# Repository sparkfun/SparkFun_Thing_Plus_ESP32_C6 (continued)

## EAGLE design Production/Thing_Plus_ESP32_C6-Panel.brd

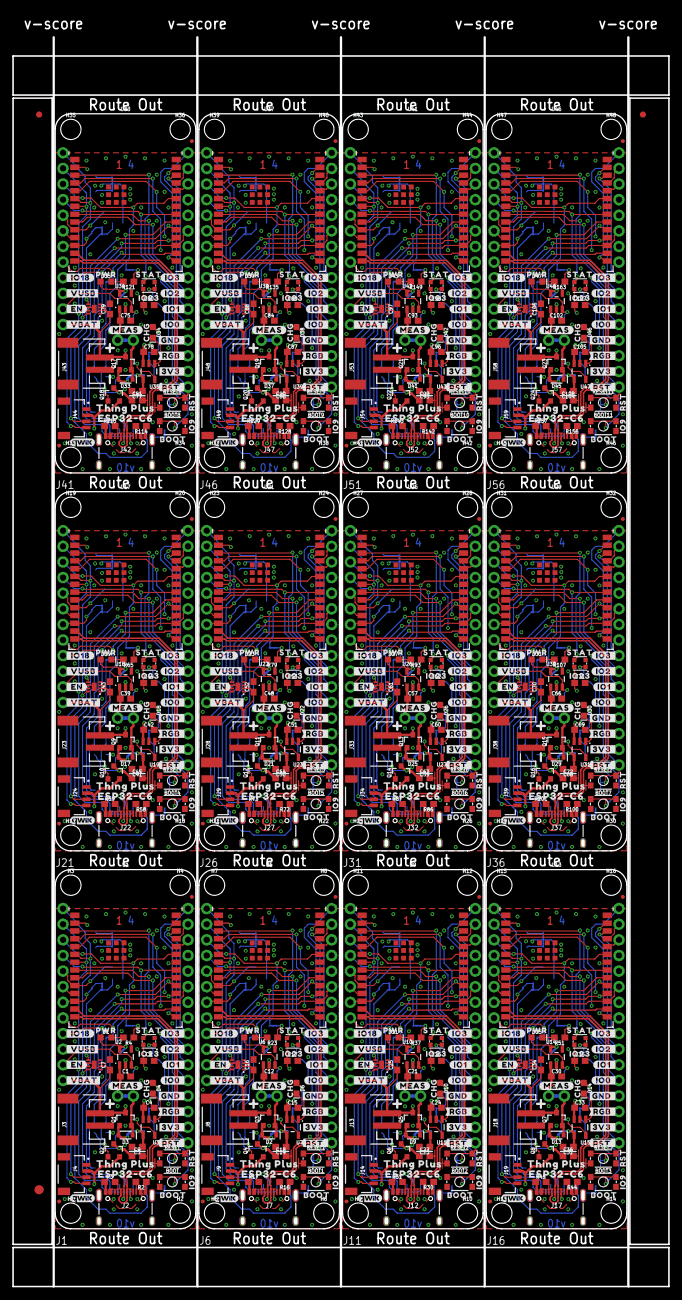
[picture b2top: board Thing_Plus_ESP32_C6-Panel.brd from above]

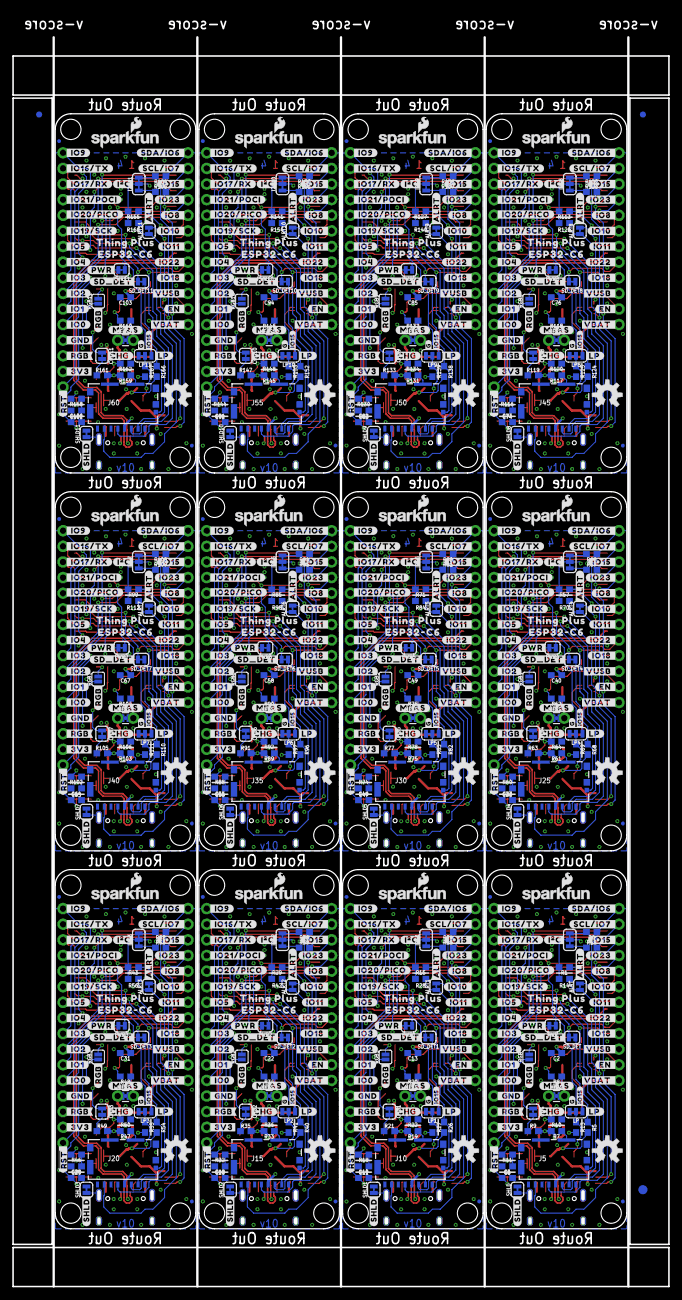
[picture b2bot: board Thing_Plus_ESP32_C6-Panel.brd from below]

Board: 4 copper layers, 106.7 x 203.2 mm, 1482 parts (831 on the bottom side), 576 nets.

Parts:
ALRT, ALRT1, ALRT2, ALRT3, ALRT4, ALRT5, ALRT6, ALRT7, ALRT8, ALRT9, ALRT10, ALRT11: JUMPER-SMT_2_NC_TRACE_SILK; SMT-JUMPER_2_NC_TRACE_SILK
BOOT, BOOT1, BOOT2, BOOT3, BOOT4, BOOT5, BOOT6, BOOT7, BOOT8, BOOT9, BOOT10, BOOT11: MOMENTARY-SWITCH-SPST-SMD-4.6X2.8MM; TACTILE_SWITCH_SMD_4.6X2.8MM
C1, C2, C3, C4, C12, C13, C14, C15, C21, C22, C23, C24, C30, C31, C32, C33, C39, C40, C41, C42, C48, C49, C50, C51, C57, C58, C59, C60, C66, C67, C68, C69, C75, C76, C77, C78, C84, C85, C86, C87, C93, C94, C95, C96, C102, C103, C104, C105: 2.2uF; 0603
C5, C7, C8, C10, C16, C17, C19, C25, C26, C28, C34, C35, C37, C43, C44, C46, C52, C53, C55, C61, C62, C64, C70, C71, C73, C79, C80, C82, C88, C89, C91, C97, C98, C100, C106, C107: 0.1uF; 0603
C6, C11, C20, C29, C38, C47, C56, C65, C74, C83, C92, C101: DNP; 0603
C9, C18, C27, C36, C45, C54, C63, C72, C81, C90, C99, C108: 10uF; 0603
CHG, CHG1, CHG2, CHG3, CHG4, CHG5, CHG6, CHG7, CHG8, CHG9, CHG10, CHG11: JUMPER-SMT_2_NC_TRACE_SILK; SMT-JUMPER_2_NC_TRACE_SILK
D1, D7, D11, D15, D19, D23, D27, D31, D35, D39, D43, D47: LED-0603
D2, D3, D9, D13, D17, D21, D25, D29, D33, D37, D41, D45: 1A/23V/620mV; SOD-323
D4, D6, D10, D14, D18, D22, D26, D30, D34, D38, D42, D46: Yellow; LED-0603
D5, D8, D12, D16, D20, D24, D28, D32, D36, D40, D44, D48: WS2812_2020; WS2812-2020
E$1, E$2, E$3, E$4: FIDUCIAL-1X2
E$5, E$6: FIDUCIAL-1.5X3
FD1, FD2, FD3, FD4, FD5, FD6, FD7, FD8, FD9, FD10, FD11, FD12, FD13, FD14, FD15, FD16, FD17, FD18, FD19, FD20, FD21, FD22, FD23, FD24, FD25, FD26, FD27, FD28, FD29, FD30, FD31, FD32, FD33, FD34, FD35, FD36, FD37, FD38, FD39, FD40, FD41, FD42, FD43, FD44, FD45, FD46, FD47, FD48: FIDUCIALUFIDUCIAL; FIDUCIAL-MICRO
H1, H2, H3, H4, H5, H6, H7, H8, H9, H10, H11, H12, H13, H14, H15, H16, H17, H18, H19, H20, H21, H22, H23, H24, H25, H26, H27, H28, H29, H30, H31, H32, H33, H34, H35, H36, H37, H38, H39, H40, H41, H42, H43, H44, H45, H46, H47, H48: STAND-OFF
I2C, I2C1, I2C2, I2C3, I2C4, I2C5, I2C6, I2C7, I2C8, I2C9, I2C10, I2C11: JUMPER-SMT_3_2-NC_TRACE_SILK; SMT-JUMPER_3_2-NC_TRACE_SILK
J1, J6, J11, J16, J21, J26, J31, J36, J41, J46, J51, J56: THING_PLUS_LOGICAL; THING_PLUS
J2, J7, J12, J17, J22, J27, J32, J37, J42, J47, J52, J57: USB-C-16P_4LAYER-PADS
J3, J8, J13, J18, J23, J28, J33, J38, J43, J48, J53, J58: JST-2-SMD
J4, J9, J14, J19, J24, J29, J34, J39, J44, J49, J54, J59: QWIIC_RIGHT_ANGLE; JST04_1MM_RA
J5, J10, J15, J20, J25, J30, J35, J40, J45, J50, J55, J60: MICRO-SDFRICTION; MICROSD_TINY
LOGO1, LOGO4, LOGO7, LOGO10, LOGO13, LOGO16, LOGO19, LOGO22, LOGO25, LOGO28, LOGO31, LOGO34: SFE_LOGO_NAME_FLAME.1_INCH; SFE_LOGO_NAME_FLAME_.1
LOGO2, LOGO5, LOGO8, LOGO11, LOGO14, LOGO17, LOGO20, LOGO23, LOGO26, LOGO29, LOGO32, LOGO35: QWIIC_LOGO_4MM; QWIIC_4MM
LOGO3, LOGO6, LOGO9, LOGO12, LOGO15, LOGO18, LOGO21, LOGO24, LOGO27, LOGO30, LOGO33, LOGO36: OSHW-LOGOM; OSHW-LOGO-M
LP, LP1, LP2, LP3, LP4, LP5, LP6, LP7, LP8, LP9, LP10, LP11: JUMPER-SMT_3_1-NC_TRACE_SILK; SMT-JUMPER_3_1-NC_TRACE_SILK
MEAS, MEAS1, MEAS2, MEAS3, MEAS4, MEAS5, MEAS6, MEAS7, MEAS8, MEAS9, MEAS10, MEAS11: JUMPER-COMBO_2_NC_TRACE; COMBO-JUMPER_2_NC_TRACE
PWR, PWR1, PWR2, PWR3, PWR4, PWR5, PWR6, PWR7, PWR8, PWR9, PWR10, PWR11: JUMPER-SMT_2_NC_TRACE_SILK; SMT-JUMPER_2_NC_TRACE_SILK
Q1, Q2, Q3, Q4, Q5, Q6, Q7, Q8, Q9, Q10, Q11, Q12, Q13, Q14, Q15, Q16, Q17, Q18, Q19, Q20, Q21, Q22, Q23, Q24: 20V/4.2A/52mΩ/1.4W; SOT23-3
R1, R5, R7, R8, R11, R13, R14, R15, R18, R19, R20, R26, R27, R28, R29, R32, R33, R34, R40, R41, R42, R43, R46, R47, R48, R54, R55, R56, R57, R60, R61, R62, R68, R69, R70, R71, R74, R75, R76, R82, R83, R84, R85, R88, R89, R90, R96, R97, R98, R99, R102, R103, R104, R110, R111, R112, R113, R116, R117, R118, R124, R125, R126, R127, R130, R131, R132, R138, R139, R140, R141, R144, R145, R146, R152, R153, R154, R155, R158, R159, R160, R166, R167, R168: 100k; 0603
R2, R3, R16, R17, R30, R31, R44, R45, R58, R59, R72, R73, R86, R87, R100, R101, R114, R115, R128, R129, R142, R143, R156, R157: 5.1k; 0603
R4, R9, R10, R21, R22, R23, R35, R36, R37, R49, R50, R51, R63, R64, R65, R77, R78, R79, R91, R92, R93, R105, R106, R107, R119, R120, R121, R133, R134, R135, R147, R148, R149, R161, R162, R163: 4.7k; 0603
R6, R12, R24, R25, R38, R39, R52, R53, R66, R67, R80, R81, R94, R95, R108, R109, R122, R123, R136, R137, R150, R151, R164, R165: 2.2k; 0603
RESET, RESET1, RESET2, RESET3, RESET4, RESET5, RESET6, RESET7, RESET8, RESET9, RESET10, RESET11: MOMENTARY-SWITCH-SPST-SMD-4.6X2.8MM; TACTILE_SWITCH_SMD_4.6X2.8MM
RGB, RGB1, RGB2, RGB3, RGB4, RGB5, RGB6, RGB7, RGB8, RGB9, RGB10, RGB11: JUMPER-SMT_2_NO_SILK; SMT-JUMPER_2_NO_SILK
SD_DET, SD_DET1, SD_DET2, SD_DET3, SD_DET4, SD_DET5, SD_DET6, SD_DET7, SD_DET8, SD_DET9, SD_DET10, SD_DET11: JUMPER-SMT_2_NC_TRACE_SILK; SMT-JUMPER_2_NC_TRACE_SILK
SHLD, SHLD1, SHLD2, SHLD3, SHLD4, SHLD5, SHLD6, SHLD7, SHLD8, SHLD9, SHLD10, SHLD11: JUMPER-SMT_2_NC_TRACE_SILK; SMT-JUMPER_2_NC_TRACE_SILK
U1, U5, U9, U13, U17, U21, U25, U29, U33, U37, U41, U45: ESP32-C6-WROOM-1-NARROW
U2, U6, U10, U14, U18, U22, U26, U30, U34, U38, U42, U46: RT9080-33GJ5; SOT23-5
U3, U7, U11, U15, U19, U23, U27, U31, U35, U39, U43, U47: MCP73831; SOT23-5
U4, U8, U12, U16, U20, U24, U28, U32, U36, U40, U44, U48: MAX17048; DFN-8
U$1, U$57, U$127, U$190, U$253, U$316, U$379, U$442, U$505, U$568, U$631, U$694: #SHLD#0
U$2, U$60, U$128, U$191, U$254, U$317, U$380, U$443, U$506, U$569, U$632, U$695: #I�C#0
U$3, U$61, U$129, U$192, U$255, U$318, U$381, U$444, U$507, U$570, U$633, U$696: #_IO18#0
U$4, U$67, U$130, U$193, U$256, U$319, U$382, U$445, U$508, U$571, U$634, U$697: #_VUSB#0
U$5, U$68, U$131, U$194, U$257, U$320, U$383, U$446, U$509, U$572, U$635, U$698: #_VBAT#0
U$6, U$69, U$132, U$195, U$258, U$321, U$384, U$447, U$510, U$573, U$636, U$699: #_EN#0
U$7, U$70, U$133, U$196, U$259, U$322, U$385, U$448, U$511, U$574, U$637, U$700: #IO3_#0
U$8, U$71, U$134, U$197, U$260, U$323, U$386, U$449, U$512, U$575, U$638, U$701: #IO2_#0
U$9, U$72, U$135, U$198, U$261, U$324, U$387, U$450, U$513, U$576, U$639, U$702: #IO1_#0
U$10, U$73, U$136, U$199, U$262, U$325, U$388, U$451, U$514, U$577, U$640, U$703: #IO0_#0
U$11, U$74, U$137, U$200, U$263, U$326, U$389, U$452, U$515, U$578, U$641, U$704: #GND_#0
U$12, U$75, U$138, U$201, U$264, U$327, U$390, U$453, U$516, U$579, U$642, U$705: #3V3_#0
U$13, U$37, U$76, U$97, U$139, U$160, U$202, U$223, U$265, U$286, U$328, U$349, U$391, U$412, U$454, U$475, U$517, U$538, U$580, U$601, U$643, U$664, U$706, U$727: ##RST#_#0
U$14, U$77, U$140, U$203, U$266, U$329, U$392, U$455, U$518, U$581, U$644, U$707: #SDA#IO6_#0
U$15, U$78, U$141, U$204, U$267, U$330, U$393, U$456, U$519, U$582, U$645, U$708: #SCL#IO7_#0
U$16, U$121, U$184, U$247, U$310, U$373, U$436, U$499, U$562, U$625, U$688, U$751: #_IO21#POCI#0
U$17, U$124, U$187, U$250, U$313, U$376, U$439, U$502, U$565, U$628, U$691, U$754: #LP#0
U$18, U$79, U$142, U$205, U$268, U$331, U$394, U$457, U$520, U$583, U$646, U$709: #IO8_#0
U$19, U$80, U$143, U$206, U$269, U$332, U$395, U$458, U$521, U$584, U$647, U$710: #IO10_#0
U$20, U$81, U$144, U$207, U$270, U$333, U$396, U$459, U$522, U$585, U$648, U$711: #IO11_#0
U$21, U$122, U$185, U$248, U$311, U$374, U$437, U$500, U$563, U$626, U$689, U$752: #_IO19#SCK#0
U$22, U$82, U$145, U$208, U$271, U$334, U$397, U$460, U$523, U$586, U$649, U$712: #IO18_#0
U$23, U$83, U$146, U$209, U$272, U$335, U$398, U$461, U$524, U$587, U$650, U$713: #_IO9#0
U$24, U$84, U$147, U$210, U$273, U$336, U$399, U$462, U$525, U$588, U$651, U$714: #_IO16#TX#0
U$25, U$85, U$148, U$211, U$274, U$337, U$400, U$463, U$526, U$589, U$652, U$715: #_IO17#RX#0
U$26, U$123, U$186, U$249, U$312, U$375, U$438, U$501, U$564, U$627, U$690, U$753: #_IO20#PICO#0
U$27, U$125, U$188, U$251, U$314, U$377, U$440, U$503, U$566, U$629, U$692, U$755: #IO15#0
U$28, U$126, U$189, U$252, U$315, U$378, U$441, U$504, U$567, U$630, U$693, U$756: #ALRT#0
U$29, U$86, U$149, U$212, U$275, U$338, U$401, U$464, U$527, U$590, U$653, U$716: #_IO5#0
U$30, U$87, U$150, U$213, U$276, U$339, U$402, U$465, U$528, U$591, U$654, U$717: #_IO4#0
U$31, U$88, U$151, U$214, U$277, U$340, U$403, U$466, U$529, U$592, U$655, U$718: #_IO3#0
U$32, U$89, U$152, U$215, U$278, U$341, U$404, U$467, U$530, U$593, U$656, U$719: #_IO2#0
U$33, U$90, U$153, U$216, U$279, U$342, U$405, U$468, U$531, U$594, U$657, U$720: #_IO1#0
U$34, U$91, U$154, U$217, U$280, U$343, U$406, U$469, U$532, U$595, U$658, U$721: #_IO0#0
U$35, U$92, U$155, U$218, U$281, U$344, U$407, U$470, U$533, U$596, U$659, U$722: #_GND#0
U$36, U$93, U$156, U$219, U$282, U$345, U$408, U$471, U$534, U$597, U$660, U$723: #_3V3#0
U$38, U$94, U$157, U$220, U$283, U$346, U$409, U$472, U$535, U$598, U$661, U$724: #VUSB_#0
U$39, U$95, U$158, U$221, U$284, U$347, U$410, U$473, U$536, U$599, U$662, U$725: #VBAT_#0
U$40, U$96, U$159, U$222, U$285, U$348, U$411, U$474, U$537, U$600, U$663, U$726: #EN_#0
U$41, U$98, U$161, U$224, U$287, U$350, U$413, U$476, U$539, U$602, U$665, U$728: #SD_DET#0
U$42, U$99, U$162, U$225, U$288, U$351, U$414, U$477, U$540, U$603, U$666, U$729: BOOT0
U$43, U$100, U$163, U$226, U$289, U$352, U$415, U$478, U$541, U$604, U$667, U$730: RST0
U$44, U$101, U$164, U$227, U$290, U$353, U$416, U$479, U$542, U$605, U$668, U$731: IO90
U$45, U$47, U$102, U$104, U$165, U$167, U$228, U$230, U$291, U$293, U$354, U$356, U$417, U$419, U$480, U$482, U$543, U$545, U$606, U$608, U$669, U$671, U$732, U$734: THING_PLUS0
U$46, U$48, U$103, U$105, U$166, U$168, U$229, U$231, U$292, U$294, U$355, U$357, U$418, U$420, U$481, U$483, U$544, U$546, U$607, U$609, U$670, U$672, U$733, U$735: ESP32#C60
U$49, U$50, U$106, U$107, U$169, U$170, U$232, U$233, U$295, U$296, U$358, U$359, U$421, U$422, U$484, U$485, U$547, U$548, U$610, U$611, U$673, U$674, U$736, U$737: #MEAS#0
U$51, U$108, U$171, U$234, U$297, U$360, U$423, U$486, U$549, U$612, U$675, U$738: #CHG#0
U$52, U$109, U$172, U$235, U$298, U$361, U$424, U$487, U$550, U$613, U$676, U$739: #PWR#0
U$53, U$110, U$173, U$236, U$299, U$362, U$425, U$488, U$551, U$614, U$677, U$740: PWR0
U$54, U$111, U$174, U$237, U$300, U$363, U$426, U$489, U$552, U$615, U$678, U$741: CHG0
U$55, U$112, U$175, U$238, U$301, U$364, U$427, U$490, U$553, U$616, U$679, U$742: STAT0
U$56, U$113, U$176, U$239, U$302, U$365, U$428, U$491, U$554, U$617, U$680, U$743: #RGB#0
U$58, U$114, U$177, U$240, U$303, U$366, U$429, U$492, U$555, U$618, U$681, U$744: #RGB_#0
U$59, U$115, U$178, U$241, U$304, U$367, U$430, U$493, U$556, U$619, U$682, U$745: #_RGB#0
U$62, U$117, U$180, U$243, U$306, U$369, U$432, U$495, U$558, U$621, U$684, U$747: IO230
U$63, U$116, U$179, U$242, U$305, U$368, U$431, U$494, U$557, U$620, U$683, U$746: #G#0
U$64, U$119, U$182, U$245, U$308, U$371, U$434, U$497, U$560, U$623, U$686, U$749: #IO23_#0
U$65, U$118, U$181, U$244, U$307, U$370, U$433, U$496, U$559, U$622, U$685, U$748: #IO15_#0
U$66, U$120, U$183, U$246, U$309, U$372, U$435, U$498, U$561, U$624, U$687, U$750: #IO22_#0

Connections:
3.3V: C2.1, D1.A, I2C.2, J1.27, J4.2, Q2.2, R1.2, R11.2, R13.2, R14.2, U1.2, U2.5
3.3V1: C13.1, D7.A, I2C1.2, J6.27, J9.2, Q4.2, R15.2, R18.2, R27.2, R28.2, U5.2, U6.5
3.3V2: C22.1, D11.A, I2C2.2, J11.27, J14.2, Q6.2, R29.2, R32.2, R41.2, R42.2, U9.2, U10.5
3.3V3: C31.1, D15.A, I2C3.2, J16.27, J19.2, Q8.2, R43.2, R46.2, R55.2, R56.2, U13.2, U14.5
3.3V4: C40.1, D19.A, I2C4.2, J21.27, J24.2, Q10.2, R57.2, R60.2, R69.2, R70.2, U17.2, U18.5
3.3V5: C49.1, D23.A, I2C5.2, J26.27, J29.2, Q12.2, R71.2, R74.2, R83.2, R84.2, U21.2, U22.5
3.3V6: C58.1, D27.A, I2C6.2, J31.27, J34.2, Q14.2, R85.2, R88.2, R97.2, R98.2, U25.2, U26.5
3.3V7: C67.1, D31.A, I2C7.2, J36.27, J39.2, Q16.2, R99.2, R102.2, R111.2, R112.2, U29.2, U30.5
3.3V8: C76.1, D35.A, I2C8.2, J41.27, J44.2, Q18.2, R113.2, R116.2, R125.2, R126.2, U33.2, U34.5
3.3V9: C85.1, D39.A, I2C9.2, J46.27, J49.2, Q20.2, R127.2, R130.2, R139.2, R140.2, U37.2, U38.5
3.3V10: C94.1, D43.A, I2C10.2, J51.27, J54.2, Q22.2, R141.2, R144.2, R153.2, R154.2, U41.2, U42.5
3.3V11: C103.1, D47.A, I2C11.2, J56.27, J59.2, Q24.2, R155.2, R158.2, R167.2, R168.2, U45.2, U46.5
ESP_EN: C5.1, J1.28, R11.1, RESET.3, RESET.4, U1.3
ESP_EN1: C10.1, J6.28, R18.1, RESET1.3, RESET1.4, U5.3
ESP_EN2: C19.1, J11.28, R32.1, RESET2.3, RESET2.4, U9.3
ESP_EN3: C28.1, J16.28, R46.1, RESET3.3, RESET3.4, U13.3
ESP_EN4: C37.1, J21.28, R60.1, RESET4.3, RESET4.4, U17.3
ESP_EN5: C46.1, J26.28, R74.1, RESET5.3, RESET5.4, U21.3
ESP_EN6: C55.1, J31.28, R88.1, RESET6.3, RESET6.4, U25.3
ESP_EN7: C64.1, J36.28, R102.1, RESET7.3, RESET7.4, U29.3
ESP_EN8: C73.1, J41.28, R116.1, RESET8.3, RESET8.4, U33.3
ESP_EN9: C82.1, J46.28, R130.1, RESET9.3, RESET9.4, U37.3
ESP_EN10: C91.1, J51.28, R144.1, RESET10.3, RESET10.4, U41.3
ESP_EN11: C100.1, J56.28, R158.1, RESET11.3, RESET11.4, U45.3
GND: BOOT.1, BOOT.2, C1.2, C2.2, C3.2, C4.2, C5.2, C6.2, C7.2, C8.2, C9.2, D5.GND, J1.25, J2.GND, J2.GND2, J3.1, J4.1, J5.6, J5.GND1, J5.GND2, J5.GND3, J5.GND4, J5.GND5, J5.GND6, LP.3, PWR.1, R2.1, R3.1, R7.1, R10.1, RESET.1, RESET.2, SHLD.2, U1.1, U1.28, U1.29, U1.30, U1.31, U1.32, U1.33, U1.34, U1.35, U1.36, U1.37, U2.2, U3.2, U4.1, U4.4, U4.6, U4.9
GND1: BOOT1.1, BOOT1.2, C10.2, C11.2, C12.2, C13.2, C14.2, C15.2, C16.2, C17.2, C18.2, D8.GND, J6.25, J7.GND, J7.GND2, J8.1, J9.1, J10.6, J10.GND1, J10.GND2, J10.GND3, J10.GND4, J10.GND5, J10.GND6, LP1.3, PWR1.1, R16.1, R17.1, R19.1, R22.1, RESET1.1, RESET1.2, SHLD1.2, U5.1, U5.28, U5.29, U5.30, U5.31, U5.32, U5.33, U5.34, U5.35, U5.36, U5.37, U6.2, U7.2, U8.1, U8.4, U8.6, U8.9
GND2: BOOT2.1, BOOT2.2, C19.2, C20.2, C21.2, C22.2, C23.2, C24.2, C25.2, C26.2, C27.2, D12.GND, J11.25, J12.GND, J12.GND2, J13.1, J14.1, J15.6, J15.GND1, J15.GND2, J15.GND3, J15.GND4, J15.GND5, J15.GND6, LP2.3, PWR2.1, R30.1, R31.1, R33.1, R36.1, RESET2.1, RESET2.2, SHLD2.2, U9.1, U9.28, U9.29, U9.30, U9.31, U9.32, U9.33, U9.34, U9.35, U9.36, U9.37, U10.2, U11.2, U12.1, U12.4, U12.6, U12.9
GND3: BOOT3.1, BOOT3.2, C28.2, C29.2, C30.2, C31.2, C32.2, C33.2, C34.2, C35.2, C36.2, D16.GND, J16.25, J17.GND, J17.GND2, J18.1, J19.1, J20.6, J20.GND1, J20.GND2, J20.GND3, J20.GND4, J20.GND5, J20.GND6, LP3.3, PWR3.1, R44.1, R45.1, R47.1, R50.1, RESET3.1, RESET3.2, SHLD3.2, U13.1, U13.28, U13.29, U13.30, U13.31, U13.32, U13.33, U13.34, U13.35, U13.36, U13.37, U14.2, U15.2, U16.1, U16.4, U16.6, U16.9
GND4: BOOT4.1, BOOT4.2, C37.2, C38.2, C39.2, C40.2, C41.2, C42.2, C43.2, C44.2, C45.2, D20.GND, J21.25, J22.GND, J22.GND2, J23.1, J24.1, J25.6, J25.GND1, J25.GND2, J25.GND3, J25.GND4, J25.GND5, J25.GND6, LP4.3, PWR4.1, R58.1, R59.1, R61.1, R64.1, RESET4.1, RESET4.2, SHLD4.2, U17.1, U17.28, U17.29, U17.30, U17.31, U17.32, U17.33, U17.34, U17.35, U17.36, U17.37, U18.2, U19.2, U20.1, U20.4, U20.6, U20.9
GND5: BOOT5.1, BOOT5.2, C46.2, C47.2, C48.2, C49.2, C50.2, C51.2, C52.2, C53.2, C54.2, D24.GND, J26.25, J27.GND, J27.GND2, J28.1, J29.1, J30.6, J30.GND1, J30.GND2, J30.GND3, J30.GND4, J30.GND5, J30.GND6, LP5.3, PWR5.1, R72.1, R73.1, R75.1, R78.1, RESET5.1, RESET5.2, SHLD5.2, U21.1, U21.28, U21.29, U21.30, U21.31, U21.32, U21.33, U21.34, U21.35, U21.36, U21.37, U22.2, U23.2, U24.1, U24.4, U24.6, U24.9
GND6: BOOT6.1, BOOT6.2, C55.2, C56.2, C57.2, C58.2, C59.2, C60.2, C61.2, C62.2, C63.2, D28.GND, J31.25, J32.GND, J32.GND2, J33.1, J34.1, J35.6, J35.GND1, J35.GND2, J35.GND3, J35.GND4, J35.GND5, J35.GND6, LP6.3, PWR6.1, R86.1, R87.1, R89.1, R92.1, RESET6.1, RESET6.2, SHLD6.2, U25.1, U25.28, U25.29, U25.30, U25.31, U25.32, U25.33, U25.34, U25.35, U25.36, U25.37, U26.2, U27.2, U28.1, U28.4, U28.6, U28.9
GND7: BOOT7.1, BOOT7.2, C64.2, C65.2, C66.2, C67.2, C68.2, C69.2, C70.2, C71.2, C72.2, D32.GND, J36.25, J37.GND, J37.GND2, J38.1, J39.1, J40.6, J40.GND1, J40.GND2, J40.GND3, J40.GND4, J40.GND5, J40.GND6, LP7.3, PWR7.1, R100.1, R101.1, R103.1, R106.1, RESET7.1, RESET7.2, SHLD7.2, U29.1, U29.28, U29.29, U29.30, U29.31, U29.32, U29.33, U29.34, U29.35, U29.36, U29.37, U30.2, U31.2, U32.1, U32.4, U32.6, U32.9
GND8: BOOT8.1, BOOT8.2, C73.2, C74.2, C75.2, C76.2, C77.2, C78.2, C79.2, C80.2, C81.2, D36.GND, J41.25, J42.GND, J42.GND2, J43.1, J44.1, J45.6, J45.GND1, J45.GND2, J45.GND3, J45.GND4, J45.GND5, J45.GND6, LP8.3, PWR8.1, R114.1, R115.1, R117.1, R120.1, RESET8.1, RESET8.2, SHLD8.2, U33.1, U33.28, U33.29, U33.30, U33.31, U33.32, U33.33, U33.34, U33.35, U33.36, U33.37, U34.2, U35.2, U36.1, U36.4, U36.6, U36.9
GND9: BOOT9.1, BOOT9.2, C82.2, C83.2, C84.2, C85.2, C86.2, C87.2, C88.2, C89.2, C90.2, D40.GND, J46.25, J47.GND, J47.GND2, J48.1, J49.1, J50.6, J50.GND1, J50.GND2, J50.GND3, J50.GND4, J50.GND5, J50.GND6, LP9.3, PWR9.1, R128.1, R129.1, R131.1, R134.1, RESET9.1, RESET9.2, SHLD9.2, U37.1, U37.28, U37.29, U37.30, U37.31, U37.32, U37.33, U37.34, U37.35, U37.36, U37.37, U38.2, U39.2, U40.1, U40.4, U40.6, U40.9
GND10: BOOT10.1, BOOT10.2, C91.2, C92.2, C93.2, C94.2, C95.2, C96.2, C97.2, C98.2, C99.2, D44.GND, J51.25, J52.GND, J52.GND2, J53.1, J54.1, J55.6, J55.GND1, J55.GND2, J55.GND3, J55.GND4, J55.GND5, J55.GND6, LP10.3, PWR10.1, R142.1, R143.1, R145.1, R148.1, RESET10.1, RESET10.2, SHLD10.2, U41.1, U41.28, U41.29, U41.30, U41.31, U41.32, U41.33, U41.34, U41.35, U41.36, U41.37, U42.2, U43.2, U44.1, U44.4, U44.6, U44.9
GND11: BOOT11.1, BOOT11.2, C100.2, C101.2, C102.2, C103.2, C104.2, C105.2, C106.2, C107.2, C108.2, D48.GND, J56.25, J57.GND, J57.GND2, J58.1, J59.1, J60.6, J60.GND1, J60.GND2, J60.GND3, J60.GND4, J60.GND5, J60.GND6, LP11.3, PWR11.1, R156.1, R157.1, R159.1, R162.1, RESET11.1, RESET11.2, SHLD11.2, U45.1, U45.28, U45.29, U45.30, U45.31, U45.32, U45.33, U45.34, U45.35, U45.36, U45.37, U46.2, U47.2, U48.1, U48.4, U48.6, U48.9
IO0: J1.24, U1.8
IO1: J1.23, U1.9
IO2: J1.22, U1.27
IO3: J1.21, U1.26
IO4: J1.20, U1.4
IO5: J1.19, U1.5
IO6: J6.20, U5.4
IO6/SDA: J1.1, J4.3, R6.1, U1.6, U4.8
IO6/SDA1: J6.1, J9.3, R24.1, U5.6, U8.8
IO6/SDA2: J11.1, J14.3, R38.1, U9.6, U12.8
IO6/SDA3: J16.1, J19.3, R52.1, U13.6, U16.8
IO6/SDA4: J21.1, J24.3, R66.1, U17.6, U20.8
IO6/SDA5: J26.1, J29.3, R80.1, U21.6, U24.8
IO6/SDA6: J31.1, J34.3, R94.1, U25.6, U28.8
IO6/SDA7: J36.1, J39.3, R108.1, U29.6, U32.8
IO6/SDA8: J41.1, J44.3, R122.1, U33.6, U36.8
IO6/SDA9: J46.1, J49.3, R136.1, U37.6, U40.8
IO6/SDA10: J51.1, J54.3, R150.1, U41.6, U44.8
IO6/SDA11: J56.1, J59.3, R164.1, U45.6, U48.8
IO7: J6.19, U5.5
IO7/SCL: J1.2, J4.4, R12.2, U1.7, U4.7
IO7/SCL1: J6.2, J9.4, R25.2, U5.7, U8.7
IO7/SCL2: J11.2, J14.4, R39.2, U9.7, U12.7
IO7/SCL3: J16.2, J19.4, R53.2, U13.7, U16.7
IO7/SCL4: J21.2, J24.4, R67.2, U17.7, U20.7
IO7/SCL5: J26.2, J29.4, R81.2, U21.7, U24.7
IO7/SCL6: J31.2, J34.4, R95.2, U25.7, U28.7
IO7/SCL7: J36.2, J39.4, R109.2, U29.7, U32.7
IO7/SCL8: J41.2, J44.4, R123.2, U33.7, U36.7
IO7/SCL9: J46.2, J49.4, R137.2, U37.7, U40.7
IO7/SCL10: J51.2, J54.4, R151.2, U41.7, U44.7
IO7/SCL11: J56.2, J59.4, R165.2, U45.7, U48.7
IO8: J1.5, R1.1, U1.10
IO9: J6.22, U5.27
IO9/BOOT: BOOT.3, BOOT.4, C6.1, J1.13, U1.15
IO9/BOOT1: BOOT1.3, BOOT1.4, C11.1, J6.13, U5.15
IO9/BOOT2: BOOT2.3, BOOT2.4, C20.1, J11.13, U9.15
IO9/BOOT3: BOOT3.3, BOOT3.4, C29.1, J16.13, U13.15
IO9/BOOT4: BOOT4.3, BOOT4.4, C38.1, J21.13, U17.15
IO9/BOOT5: BOOT5.3, BOOT5.4, C47.1, J26.13, U21.15
IO9/BOOT6: BOOT6.3, BOOT6.4, C56.1, J31.13, U25.15
IO9/BOOT7: BOOT7.3, BOOT7.4, C65.1, J36.13, U29.15
IO9/BOOT8: BOOT8.3, BOOT8.4, C74.1, J41.13, U33.15
IO9/BOOT9: BOOT9.3, BOOT9.4, C83.1, J46.13, U37.15
IO9/BOOT10: BOOT10.3, BOOT10.4, C92.1, J51.13, U41.15
IO9/BOOT11: BOOT11.3, BOOT11.4, C101.1, J56.13, U45.15
IO10: J1.6, U1.11
IO11: J6.21, U5.26
IO11/!ALRT!: ALRT.2, J1.7, U1.12
IO11/!ALRT!1: ALRT1.2, J6.7, U5.12
IO11/!ALRT!2: ALRT2.2, J11.7, U9.12
IO11/!ALRT!3: ALRT3.2, J16.7, U13.12
IO11/!ALRT!4: ALRT4.2, J21.7, U17.12
IO11/!ALRT!5: ALRT5.2, J26.7, U21.12
IO11/!ALRT!6: ALRT6.2, J31.7, U25.12
IO11/!ALRT!7: ALRT7.2, J36.7, U29.12
IO11/!ALRT!8: ALRT8.2, J41.7, U33.12
IO11/!ALRT!9: ALRT9.2, J46.7, U37.12
IO11/!ALRT!10: ALRT10.2, J51.7, U41.12
IO11/!ALRT!11: ALRT11.2, J56.7, U45.12
IO12: J6.5, R15.1, U5.10
IO13: J6.24, U5.8
IO14: J6.23, U5.9
IO15: J6.6, U5.11
IO15/LP: J1.3, LP.1, U1.23
IO15/LP1: J6.3, LP1.1, U5.23
IO15/LP2: J11.3, LP2.1, U9.23
IO15/LP3: J16.3, LP3.1, U13.23
IO15/LP4: J21.3, LP4.1, U17.23
IO15/LP5: J26.3, LP5.1, U21.23
IO15/LP6: J31.3, LP6.1, U25.23
IO15/LP7: J36.3, LP7.1, U29.23
IO15/LP8: J41.3, LP8.1, U33.23
IO15/LP9: J46.3, LP9.1, U37.23
IO15/LP10: J51.3, LP10.1, U41.23
IO15/LP11: J56.3, LP11.1, U45.23
IO16: J11.20, U9.4
IO16/TX: J1.14, U1.25
IO16/TX1: J6.14, U5.25
IO16/TX2: J11.14, U9.25
IO16/TX3: J16.14, U13.25
IO16/TX4: J21.14, U17.25
IO16/TX5: J26.14, U21.25
IO16/TX6: J31.14, U25.25
IO16/TX7: J36.14, U29.25
IO16/TX8: J41.14, U33.25
IO16/TX9: J46.14, U37.25
IO16/TX10: J51.14, U41.25
IO16/TX11: J56.14, U45.25
IO17: J11.19, U9.5
IO17/RX: J1.15, U1.24
IO17/RX1: J6.15, U5.24
IO17/RX2: J11.15, U9.24
IO17/RX3: J16.15, U13.24
IO17/RX4: J21.15, U17.24
IO17/RX5: J26.15, U21.24
IO17/RX6: J31.15, U25.24
IO17/RX7: J36.15, U29.24
IO17/RX8: J41.15, U33.24
IO17/RX9: J46.15, U37.24
IO17/RX10: J51.15, U41.24
IO17/RX11: J56.15, U45.24
IO18: J11.22, U9.27
IO18/!CS!: J1.9, J5.2, U1.16
IO18/!CS!1: J6.9, J10.2, U5.16
IO18/!CS!2: J11.9, J15.2, U9.16
IO18/!CS!3: J16.9, J20.2, U13.16
IO18/!CS!4: J21.9, J25.2, U17.16
IO18/!CS!5: J26.9, J30.2, U21.16
IO18/!CS!6: J31.9, J35.2, U25.16
IO18/!CS!7: J36.9, J40.2, U29.16
IO18/!CS!8: J41.9, J45.2, U33.16
IO18/!CS!9: J46.9, J50.2, U37.16
IO18/!CS!10: J51.9, J55.2, U41.16
IO18/!CS!11: J56.9, J60.2, U45.16
IO19: J11.21, U9.26
IO19/SCK: J1.18, J5.5, U1.17
IO19/SCK1: J6.18, J10.5, U5.17
IO19/SCK2: J11.18, J15.5, U9.17
IO19/SCK3: J16.18, J20.5, U13.17
IO19/SCK4: J21.18, J25.5, U17.17
IO19/SCK5: J26.18, J30.5, U21.17
IO19/SCK6: J31.18, J35.5, U25.17
IO19/SCK7: J36.18, J40.5, U29.17
IO19/SCK8: J41.18, J45.5, U33.17
IO19/SCK9: J46.18, J50.5, U37.17
IO19/SCK10: J51.18, J55.5, U41.17
IO19/SCK11: J56.18, J60.5, U45.17
IO20: J11.5, R29.1, U9.10
IO20/PICO: J1.17, J5.3, U1.18
IO20/PICO1: J6.17, J10.3, U5.18
IO20/PICO2: J11.17, J15.3, U9.18
IO20/PICO3: J16.17, J20.3, U13.18
IO20/PICO4: J21.17, J25.3, U17.18
IO20/PICO5: J26.17, J30.3, U21.18
IO20/PICO6: J31.17, J35.3, U25.18
IO20/PICO7: J36.17, J40.3, U29.18
IO20/PICO8: J41.17, J45.3, U33.18
IO20/PICO9: J46.17, J50.3, U37.18
IO20/PICO10: J51.17, J55.3, U41.18
IO20/PICO11: J56.17, J60.3, U45.18
IO21: J11.24, U9.8
IO21/POCI: J1.16, J5.7, U1.19
IO21/POCI1: J6.16, J10.7, U5.19
IO21/POCI2: J11.16, J15.7, U9.19
IO21/POCI3: J16.16, J20.7, U13.19
IO21/POCI4: J21.16, J25.7, U17.19
IO21/POCI5: J26.16, J30.7, U21.19
IO21/POCI6: J31.16, J35.7, U25.19
IO21/POCI7: J36.16, J40.7, U29.19
IO21/POCI8: J41.16, J45.7, U33.19
IO21/POCI9: J46.16, J50.7, U37.19
IO21/POCI10: J51.16, J55.7, U41.19
IO21/POCI11: J56.16, J60.7, U45.19
IO22: J11.23, U9.9
IO22/!SD_DET!: J1.8, SD_DET.2, U1.20
IO22/!SD_DET!1: J6.8, SD_DET1.2, U5.20
IO22/!SD_DET!2: J11.8, SD_DET2.2, U9.20
IO22/!SD_DET!3: J16.8, SD_DET3.2, U13.20
IO22/!SD_DET!4: J21.8, SD_DET4.2, U17.20
IO22/!SD_DET!5: J26.8, SD_DET5.2, U21.20
IO22/!SD_DET!6: J31.8, SD_DET6.2, U25.20
IO22/!SD_DET!7: J36.8, SD_DET7.2, U29.20
IO22/!SD_DET!8: J41.8, SD_DET8.2, U33.20
IO22/!SD_DET!9: J46.8, SD_DET9.2, U37.20
IO22/!SD_DET!10: J51.8, SD_DET10.2, U41.20
IO22/!SD_DET!11: J56.8, SD_DET11.2, U45.20
IO23: J11.6, U9.11
IO23/STAT: D5.DI, J1.4, U1.21
IO23/STAT1: D8.DI, J6.4, U5.21
IO23/STAT2: D12.DI, J11.4, U9.21
IO23/STAT3: D16.DI, J16.4, U13.21
IO23/STAT4: D20.DI, J21.4, U17.21
IO23/STAT5: D24.DI, J26.4, U21.21
IO23/STAT6: D28.DI, J31.4, U25.21
IO23/STAT7: D32.DI, J36.4, U29.21
IO23/STAT8: D36.DI, J41.4, U33.21
IO23/STAT9: D40.DI, J46.4, U37.21
IO23/STAT10: D44.DI, J51.4, U41.21
IO23/STAT11: D48.DI, J56.4, U45.21
IO24: J16.20, U13.4
IO25: J16.19, U13.5
IO26: J16.22, U13.27
IO27: J16.21, U13.26
IO28: J16.5, R43.1, U13.10
IO29: J16.24, U13.8
IO30: J16.23, U13.9
IO31: J16.6, U13.11
IO32: J21.20, U17.4
IO33: J21.19, U17.5
IO34: J21.22, U17.27
IO35: J21.21, U17.26
IO36: J21.5, R57.1, U17.10
IO37: J21.24, U17.8
IO38: J21.23, U17.9
IO39: J21.6, U17.11
IO40: J26.20, U21.4
IO41: J26.19, U21.5
IO42: J26.22, U21.27
IO43: J26.21, U21.26
IO44: J26.5, R71.1, U21.10
IO45: J26.24, U21.8
IO46: J26.23, U21.9
IO47: J26.6, U21.11
IO48: J31.20, U25.4
IO49: J31.19, U25.5
IO50: J31.22, U25.27
IO51: J31.21, U25.26
IO52: J31.5, R85.1, U25.10
IO53: J31.24, U25.8
IO54: J31.23, U25.9
IO55: J31.6, U25.11
IO56: J36.20, U29.4
IO57: J36.19, U29.5
IO58: J36.22, U29.27
IO59: J36.21, U29.26
IO60: J36.5, R99.1, U29.10
IO61: J36.24, U29.8
IO62: J36.23, U29.9
IO63: J36.6, U29.11
IO64: J41.20, U33.4
IO65: J41.19, U33.5
IO66: J41.22, U33.27
IO67: J41.21, U33.26
IO68: J41.5, R113.1, U33.10
IO69: J41.24, U33.8
IO70: J41.23, U33.9
IO71: J41.6, U33.11
IO72: J46.20, U37.4
IO73: J46.19, U37.5
IO74: J46.22, U37.27
IO75: J46.21, U37.26
IO76: J46.5, R127.1, U37.10
IO77: J46.24, U37.8
IO78: J46.23, U37.9
IO79: J46.6, U37.11
IO80: J51.20, U41.4
IO81: J51.19, U41.5
IO82: J51.22, U41.27
IO83: J51.21, U41.26
IO84: J51.5, R141.1, U41.10
IO85: J51.24, U41.8
IO86: J51.23, U41.9
IO87: J51.6, U41.11
IO88: J56.20, U45.4
IO89: J56.19, U45.5
IO90: J56.22, U45.27
IO91: J56.21, U45.26
IO92: J56.5, R155.1, U45.10
IO93: J56.24, U45.8
IO94: J56.23, U45.9
IO95: J56.6, U45.11
LED_DO: J1.26, RGB.1
LED_DO1: J6.26, RGB1.1
LED_DO2: J11.26, RGB2.1
LED_DO3: J16.26, RGB3.1
LED_DO4: J21.26, RGB4.1
LED_DO5: J26.26, RGB5.1
LED_DO6: J31.26, RGB6.1
LED_DO7: J36.26, RGB7.1
LED_DO8: J41.26, RGB8.1
LED_DO9: J46.26, RGB9.1
LED_DO10: J51.26, RGB10.1
LED_DO11: J56.26, RGB11.1
unnamed: D1.C, R4.2
unnamed: PWR.2, R4.1
unnamed: J5.9, R5.1, SD_DET.1
unnamed: D3.C, MEAS.1, MEAS.3, Q1.2
unnamed: I2C.3, R6.2
unnamed: I2C.1, R12.1
unnamed: J2.B5, R2.2
unnamed: J2.A5, R3.2
unnamed: C1.1, MEAS.2, MEAS.4, R8.1, U2.1
unnamed: D4.C, U3.1
unnamed: CHG.1, D4.A
unnamed: CHG.2, R9.1
unnamed: R10.2, U3.5
unnamed: D5.DO, RGB.2
unnamed: J7.B5, R16.2
unnamed: LP.2, Q2.1, R13.1
unnamed: ALRT.1, R14.1, U4.5
unnamed: J7.A5, R17.2
unnamed: C12.1, MEAS1.2, MEAS1.4, R20.1, U6.1
unnamed: D6.C, U7.1
unnamed: CHG1.1, D6.A
unnamed: CHG1.2, R21.1
unnamed: R22.2, U7.5
unnamed: I2C1.3, R24.2
unnamed: I2C1.1, R25.1
unnamed: J10.9, R26.1, SD_DET1.1
unnamed: D2.C, MEAS1.1, MEAS1.3, Q3.2
unnamed: D7.C, R23.2
unnamed: PWR1.2, R23.1
unnamed: D8.DO, RGB1.2
unnamed: LP1.2, Q4.1, R27.1
unnamed: ALRT1.1, R28.1, U8.5
unnamed: J12.B5, R30.2
unnamed: J12.A5, R31.2
unnamed: C21.1, MEAS2.2, MEAS2.4, R34.1, U10.1
unnamed: D10.C, U11.1
unnamed: CHG2.1, D10.A
unnamed: CHG2.2, R35.1
unnamed: R36.2, U11.5
unnamed: I2C2.3, R38.2
unnamed: I2C2.1, R39.1
unnamed: J15.9, R40.1, SD_DET2.1
unnamed: D9.C, MEAS2.1, MEAS2.3, Q5.2
unnamed: D11.C, R37.2
unnamed: PWR2.2, R37.1
unnamed: D12.DO, RGB2.2
unnamed: LP2.2, Q6.1, R41.1
unnamed: ALRT2.1, R42.1, U12.5
unnamed: J17.B5, R44.2
unnamed: J17.A5, R45.2
unnamed: C30.1, MEAS3.2, MEAS3.4, R48.1, U14.1
unnamed: D14.C, U15.1
unnamed: CHG3.1, D14.A
unnamed: CHG3.2, R49.1
unnamed: R50.2, U15.5
unnamed: I2C3.3, R52.2
unnamed: I2C3.1, R53.1
unnamed: J20.9, R54.1, SD_DET3.1
unnamed: D13.C, MEAS3.1, MEAS3.3, Q7.2
unnamed: D15.C, R51.2
unnamed: PWR3.2, R51.1
unnamed: D16.DO, RGB3.2
unnamed: LP3.2, Q8.1, R55.1
unnamed: ALRT3.1, R56.1, U16.5
unnamed: J22.B5, R58.2
unnamed: J22.A5, R59.2
unnamed: C39.1, MEAS4.2, MEAS4.4, R62.1, U18.1
unnamed: D18.C, U19.1
unnamed: CHG4.1, D18.A
unnamed: CHG4.2, R63.1
unnamed: R64.2, U19.5
unnamed: I2C4.3, R66.2
unnamed: I2C4.1, R67.1
unnamed: J25.9, R68.1, SD_DET4.1
unnamed: D17.C, MEAS4.1, MEAS4.3, Q9.2
unnamed: D19.C, R65.2
unnamed: PWR4.2, R65.1
unnamed: D20.DO, RGB4.2
unnamed: LP4.2, Q10.1, R69.1
unnamed: ALRT4.1, R70.1, U20.5
unnamed: J27.B5, R72.2
unnamed: J27.A5, R73.2
unnamed: C48.1, MEAS5.2, MEAS5.4, R76.1, U22.1
unnamed: D22.C, U23.1
unnamed: CHG5.1, D22.A
unnamed: CHG5.2, R77.1
unnamed: R78.2, U23.5
unnamed: I2C5.3, R80.2
unnamed: I2C5.1, R81.1
unnamed: J30.9, R82.1, SD_DET5.1
unnamed: D21.C, MEAS5.1, MEAS5.3, Q11.2
unnamed: D23.C, R79.2
unnamed: PWR5.2, R79.1
unnamed: D24.DO, RGB5.2
unnamed: LP5.2, Q12.1, R83.1
unnamed: ALRT5.1, R84.1, U24.5
unnamed: J32.B5, R86.2
unnamed: J32.A5, R87.2
unnamed: C57.1, MEAS6.2, MEAS6.4, R90.1, U26.1
unnamed: D26.C, U27.1
unnamed: CHG6.1, D26.A
unnamed: CHG6.2, R91.1
unnamed: R92.2, U27.5
unnamed: I2C6.3, R94.2
unnamed: I2C6.1, R95.1
unnamed: J35.9, R96.1, SD_DET6.1
unnamed: D25.C, MEAS6.1, MEAS6.3, Q13.2
unnamed: D27.C, R93.2
unnamed: PWR6.2, R93.1
unnamed: D28.DO, RGB6.2
unnamed: LP6.2, Q14.1, R97.1
unnamed: ALRT6.1, R98.1, U28.5
unnamed: J37.B5, R100.2
unnamed: J37.A5, R101.2
unnamed: C66.1, MEAS7.2, MEAS7.4, R104.1, U30.1
unnamed: D30.C, U31.1
unnamed: CHG7.1, D30.A
unnamed: CHG7.2, R105.1
unnamed: R106.2, U31.5
unnamed: I2C7.3, R108.2
unnamed: I2C7.1, R109.1
unnamed: J40.9, R110.1, SD_DET7.1
unnamed: D29.C, MEAS7.1, MEAS7.3, Q15.2
unnamed: D31.C, R107.2
unnamed: PWR7.2, R107.1
unnamed: D32.DO, RGB7.2
unnamed: LP7.2, Q16.1, R111.1
unnamed: ALRT7.1, R112.1, U32.5
unnamed: J42.B5, R114.2
unnamed: J42.A5, R115.2
unnamed: C75.1, MEAS8.2, MEAS8.4, R118.1, U34.1
unnamed: D34.C, U35.1
unnamed: CHG8.1, D34.A
unnamed: CHG8.2, R119.1
unnamed: R120.2, U35.5
unnamed: I2C8.3, R122.2
unnamed: I2C8.1, R123.1
unnamed: J45.9, R124.1, SD_DET8.1
unnamed: D33.C, MEAS8.1, MEAS8.3, Q17.2
unnamed: D35.C, R121.2
unnamed: PWR8.2, R121.1
unnamed: D36.DO, RGB8.2
unnamed: LP8.2, Q18.1, R125.1
unnamed: ALRT8.1, R126.1, U36.5
unnamed: J47.B5, R128.2
unnamed: J47.A5, R129.2
unnamed: C84.1, MEAS9.2, MEAS9.4, R132.1, U38.1
unnamed: D38.C, U39.1
unnamed: CHG9.1, D38.A
unnamed: CHG9.2, R133.1
unnamed: R134.2, U39.5
unnamed: I2C9.3, R136.2
unnamed: I2C9.1, R137.1
unnamed: J50.9, R138.1, SD_DET9.1
unnamed: D37.C, MEAS9.1, MEAS9.3, Q19.2
unnamed: D39.C, R135.2
unnamed: PWR9.2, R135.1
unnamed: D40.DO, RGB9.2
unnamed: LP9.2, Q20.1, R139.1
unnamed: ALRT9.1, R140.1, U40.5
unnamed: J52.B5, R142.2
unnamed: J52.A5, R143.2
unnamed: C93.1, MEAS10.2, MEAS10.4, R146.1, U42.1
unnamed: D42.C, U43.1
unnamed: CHG10.1, D42.A
unnamed: CHG10.2, R147.1
unnamed: R148.2, U43.5
unnamed: I2C10.3, R150.2
unnamed: I2C10.1, R151.1
unnamed: J55.9, R152.1, SD_DET10.1
unnamed: D41.C, MEAS10.1, MEAS10.3, Q21.2
unnamed: D43.C, R149.2
unnamed: PWR10.2, R149.1
unnamed: D44.DO, RGB10.2
unnamed: LP10.2, Q22.1, R153.1
unnamed: ALRT10.1, R154.1, U44.5
unnamed: J57.B5, R156.2
unnamed: J57.A5, R157.2
unnamed: C102.1, MEAS11.2, MEAS11.4, R160.1, U46.1
unnamed: D46.C, U47.1
unnamed: CHG11.1, D46.A
unnamed: CHG11.2, R161.1
unnamed: R162.2, U47.5
unnamed: I2C11.3, R164.2
unnamed: I2C11.1, R165.1
unnamed: J60.9, R166.1, SD_DET11.1
unnamed: D45.C, MEAS11.1, MEAS11.3, Q23.2
unnamed: D47.C, R163.2
unnamed: PWR11.2, R163.1
unnamed: D48.DO, RGB11.2
unnamed: LP11.2, Q24.1, R167.1
unnamed: ALRT11.1, R168.1, U48.5
SHLD: J2.SHLD1, J2.SHLD2, J2.SHLD3, J2.SHLD4, SHLD.1
SHLD1: J7.SHLD1, J7.SHLD2, J7.SHLD3, J7.SHLD4, SHLD1.1
SHLD2: J12.SHLD1, J12.SHLD2, J12.SHLD3, J12.SHLD4, SHLD2.1
SHLD3: J17.SHLD1, J17.SHLD2, J17.SHLD3, J17.SHLD4, SHLD3.1
SHLD4: J22.SHLD1, J22.SHLD2, J22.SHLD3, J22.SHLD4, SHLD4.1
SHLD5: J27.SHLD1, J27.SHLD2, J27.SHLD3, J27.SHLD4, SHLD5.1
SHLD6: J32.SHLD1, J32.SHLD2, J32.SHLD3, J32.SHLD4, SHLD6.1
SHLD7: J37.SHLD1, J37.SHLD2, J37.SHLD3, J37.SHLD4, SHLD7.1
SHLD8: J42.SHLD1, J42.SHLD2, J42.SHLD3, J42.SHLD4, SHLD8.1
SHLD9: J47.SHLD1, J47.SHLD2, J47.SHLD3, J47.SHLD4, SHLD9.1
SHLD10: J52.SHLD1, J52.SHLD2, J52.SHLD3, J52.SHLD4, SHLD10.1
SHLD11: J57.SHLD1, J57.SHLD2, J57.SHLD3, J57.SHLD4, SHLD11.1
USB_N: J2.A7, J2.B7, U1.13
USB_N1: J7.A7, J7.B7, U5.13
USB_N2: J12.A7, J12.B7, U9.13
USB_N3: J17.A7, J17.B7, U13.13
USB_N4: J22.A7, J22.B7, U17.13
USB_N5: J27.A7, J27.B7, U21.13
USB_N6: J32.A7, J32.B7, U25.13
USB_N7: J37.A7, J37.B7, U29.13
USB_N8: J42.A7, J42.B7, U33.13
USB_N9: J47.A7, J47.B7, U37.13
USB_N10: J52.A7, J52.B7, U41.13
USB_N11: J57.A7, J57.B7, U45.13
USB_P: J2.A6, J2.B6, U1.14
USB_P1: J7.A6, J7.B6, U5.14
USB_P2: J12.A6, J12.B6, U9.14
USB_P3: J17.A6, J17.B6, U13.14
USB_P4: J22.A6, J22.B6, U17.14
USB_P5: J27.A6, J27.B6, U21.14
USB_P6: J32.A6, J32.B6, U25.14
USB_P7: J37.A6, J37.B6, U29.14
USB_P8: J42.A6, J42.B6, U33.14
USB_P9: J47.A6, J47.B6, U37.14
USB_P10: J52.A6, J52.B6, U41.14
USB_P11: J57.A6, J57.B6, U45.14
VOUT: C8.1, C9.1, D5.VCC, J5.4, Q2.3, R5.2
VOUT1: C17.1, C18.1, D8.VCC, J10.4, Q4.3, R26.2
VOUT2: C26.1, C27.1, D12.VCC, J15.4, Q6.3, R40.2
VOUT3: C35.1, C36.1, D16.VCC, J20.4, Q8.3, R54.2
VOUT4: C44.1, C45.1, D20.VCC, J25.4, Q10.3, R68.2
VOUT5: C53.1, C54.1, D24.VCC, J30.4, Q12.3, R82.2
VOUT6: C62.1, C63.1, D28.VCC, J35.4, Q14.3, R96.2
VOUT7: C71.1, C72.1, D32.VCC, J40.4, Q16.3, R110.2
VOUT8: C80.1, C81.1, D36.VCC, J45.4, Q18.3, R124.2
VOUT9: C89.1, C90.1, D40.VCC, J50.4, Q20.3, R138.2
VOUT10: C98.1, C99.1, D44.VCC, J55.4, Q22.3, R152.2
VOUT11: C107.1, C108.1, D48.VCC, J60.4, Q24.3, R166.2
VREG_EN: J1.11, R8.2, U2.3
VREG_EN1: J6.11, R20.2, U6.3
VREG_EN2: J11.11, R34.2, U10.3
VREG_EN3: J16.11, R48.2, U14.3
VREG_EN4: J21.11, R62.2, U18.3
VREG_EN5: J26.11, R76.2, U22.3
VREG_EN6: J31.11, R90.2, U26.3
VREG_EN7: J36.11, R104.2, U30.3
VREG_EN8: J41.11, R118.2, U34.3
VREG_EN9: J46.11, R132.2, U38.3
VREG_EN10: J51.11, R146.2, U42.3
VREG_EN11: J56.11, R160.2, U46.3
V_BATT: C4.1, C7.1, J1.12, J3.2, Q1.3, U3.3, U4.2, U4.3
V_BATT1: C15.1, C16.1, J6.12, J8.2, Q3.3, U7.3, U8.2, U8.3
V_BATT2: C24.1, C25.1, J11.12, J13.2, Q5.3, U11.3, U12.2, U12.3
V_BATT3: C33.1, C34.1, J16.12, J18.2, Q7.3, U15.3, U16.2, U16.3
V_BATT4: C42.1, C43.1, J21.12, J23.2, Q9.3, U19.3, U20.2, U20.3
V_BATT5: C51.1, C52.1, J26.12, J28.2, Q11.3, U23.3, U24.2, U24.3
V_BATT6: C60.1, C61.1, J31.12, J33.2, Q13.3, U27.3, U28.2, U28.3
V_BATT7: C69.1, C70.1, J36.12, J38.2, Q15.3, U31.3, U32.2, U32.3
V_BATT8: C78.1, C79.1, J41.12, J43.2, Q17.3, U35.3, U36.2, U36.3
V_BATT9: C87.1, C88.1, J46.12, J48.2, Q19.3, U39.3, U40.2, U40.3
V_BATT10: C96.1, C97.1, J51.12, J53.2, Q21.3, U43.3, U44.2, U44.3
V_BATT11: C105.1, C106.1, J56.12, J58.2, Q23.3, U47.3, U48.2, U48.3
V_USB: C3.1, D3.A, J1.10, J2.VBUS1, J2.VBUS2, Q1.1, R7.2, R9.2, U3.4
V_USB1: C14.1, D2.A, J6.10, J7.VBUS1, J7.VBUS2, Q3.1, R19.2, R21.2, U7.4
V_USB2: C23.1, D9.A, J11.10, J12.VBUS1, J12.VBUS2, Q5.1, R33.2, R35.2, U11.4
V_USB3: C32.1, D13.A, J16.10, J17.VBUS1, J17.VBUS2, Q7.1, R47.2, R49.2, U15.4
V_USB4: C41.1, D17.A, J21.10, J22.VBUS1, J22.VBUS2, Q9.1, R61.2, R63.2, U19.4
V_USB5: C50.1, D21.A, J26.10, J27.VBUS1, J27.VBUS2, Q11.1, R75.2, R77.2, U23.4
V_USB6: C59.1, D25.A, J31.10, J32.VBUS1, J32.VBUS2, Q13.1, R89.2, R91.2, U27.4
V_USB7: C68.1, D29.A, J36.10, J37.VBUS1, J37.VBUS2, Q15.1, R103.2, R105.2, U31.4
V_USB8: C77.1, D33.A, J41.10, J42.VBUS1, J42.VBUS2, Q17.1, R117.2, R119.2, U35.4
V_USB9: C86.1, D37.A, J46.10, J47.VBUS1, J47.VBUS2, Q19.1, R131.2, R133.2, U39.4
V_USB10: C95.1, D41.A, J51.10, J52.VBUS1, J52.VBUS2, Q21.1, R145.2, R147.2, U43.4
V_USB11: C104.1, D45.A, J56.10, J57.VBUS1, J57.VBUS2, Q23.1, R159.2, R161.2, U47.4

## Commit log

2023-06-20 Add ESP32-C6 documents
    SoC datasheet
    Module datasheet
    Hardware design guidelines
    Technical reference manual
2023-06-20 Add initial hardware library
2023-06-21 Add initial design
    Schematic needs to be organized
    SD connector needs to be routed, and have a couple pins assigned
2023-06-26 Finish initial schematic and layout
    Organized schematic
    Rearranged power circuitry to make routing other components easier
    Finished routing board
2023-06-28 Design review updates
    Add measures
    Add ordering instructions
    Add notes about jumpers
    Add voltage regulator parameters
    Rearrange LED section in schematic
2023-06-29 Design review updates
    Add RGB label to NC pin
    Move CHG LED to make room for RGB label
    Optimize GND pours
    Add GND vias
    Fix acid traps
2023-06-29 Design review updates
    Add fiducials
    Add top mounting holes under ESP32-C6 antenna
    Move OSHW logo and make bigger
    Change RGB jumper to NO
2023-06-29 Add power control to uSD card
    Also add 10uF cap for uSD card
    And add boot button text
2023-06-29 Add silk lines between passive components
2023-06-29 Checklist updates
    Add version number to copper
    Fix dimension lines to be exactly on grid
    Add PROD_ID to ESP32-C6 narrow device
    Add layer numbers to copper
    Add silk labels to SD_P jumper
2023-06-29 Add v01 panel files
2023-07-31 v10 updates
    Change pinout of GPIO 15-23 (SDIO pins have funky behavior when not configured)
    Connect fuel gauge alert pin
    Move SD power control to own circuit that creates VOUT net
    Change STAT LED to get powered from VOUT
    Change RGB jumper to NC
2023-07-31 Bump version number to v10
2023-08-01 Design review updates
    Change schematic frame to ledger
    Fix acid trap
    Approve DRC errors on jumpers
2023-08-01 Add v10 panel files
2023-08-01 Change RGB jumper to NO
    Won't violate the form factor standard by default this time!
    Also update panel files
2023-08-01 Initial Docs commit
    Adding background files & first draft of documentation markdown files.
2023-08-15 Fix schematic note about RGB jumper
2023-09-19 Change C6 to DNP
    Rise time was slow, causing chip to run bootloader instead of booting from flash
2024-01-17 Docs update
    Adding board files, common img & updating software sections.
2024-01-19 Photo Update
    Adding photos & photo links to hardware overview.
2024-01-23 Minor fixes
    Fixing photo links & other minor issues. Completing Resources page.
2024-01-30 Docs Update and review
    Final photos added and initial content functionality review/edits.
2024-01-31 Update README.md
    Update README.md from initial commit.
2024-01-31 Docs Update
    Example code and software setup update. Adding RGB example and reworking boards package install instructions.
2024-02-06 Docs Review
    Final review updates. Switching to updated "Print View" option for single page.
2024-02-13 Update introduction.md
    Adding product showcase video embed.
2024-02-13 Deployed 5b99364 with MkDocs version: 1.5.3
2024-07-09 Espressif Boards Package Update
    Updating software setup & examples with espressif Arduino Boards v3 release.
2024-07-09 Deployed a038f52 with MkDocs version: 1.6.0
2024-10-25 Update mkdocs.yml
    Analytics update
2024-10-25 Deployed fb7352f with MkDocs version: 1.6.1
